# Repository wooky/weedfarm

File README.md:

# weedfarm
An overcomplicated, low-cost replacement for the VegeHome Jardin Pro PCB which got damaged due to water leaking from the water reservoir.

## Features
Features of this package include:
* Activating the pump for 1 minute every 30 minutes
* User-configurable time to turn the lamp on and off
* Driven by an external Android device connected to the custom PCB over USB, which holds the schedule and user configuration
* Ability to charge said device over USB

## Structure
This package is split up into subdirectories:
* pcb: the actual PCB to be manufactured and populated
* firmware: the extra firmware code that would need to be loaded onto the microcontroller on the PCB; it switches the pump and lamp when commanded by the Android device
* android: an Android module which holds the pump and lamp schedule and is used to connect, monitor, and control the PCB over a USB connection

## Old Versions
[esphome](https://github.com/wooky/weedfarm/tree/esphome): a reusable package that can be used on an ESPHome installation which controls everything (but is bulky and only works over WiFi)

## License
This project is licensed under the GNU Affero General Public License v3.0. See [LICENSE](LICENSE) for details.

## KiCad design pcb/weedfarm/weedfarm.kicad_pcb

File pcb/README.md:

# PCB

Replacement controller board for the VegeHome Jardin Pro. It mounts where the original board was. The Android phone holds the schedule, and this board only switches the loads when the phone tells it to.

## Manufacturing

- Designed in EasyEDA, then manufactured and assembled by JLCPCB.
- Prefer JLCPCB basic parts where possible, to avoid extended-part setup fees.
- The barrel jack and USB-A connector are soldered by hand, not by JLCPCB.
- JLCPCB has no MCU in its basic library. The CH32X035G8U6 (C7437027) is an extended part, so it adds the extended-part setup fee.

## Power

| Rail | Source | Feeds |
|------|--------|-------|
| 12V | DC adapter via barrel jack, through a reverse-polarity Schottky (SS54) | Pump; external lamp booster; buck regulator |
| 5V | LM2596S-ADJ buck from 12V, set to about 5.3V | 3.3V LDO; USB-A VBUS through a Schottky (SS34), so VBUS sits near 5V |
| 3.3V | XC6206P332MR LDO from 5V | CH32X035 |

The diode between 5V and VBUS drops the buck's 5.3V to about 5V and stops anything plugged into the USB port from back-feeding the buck. The board needs the 12V adapter to run, including while it's being programmed.

## Microcontroller

- CH32X035G8U6 (WCH, RISC-V, 4x4mm QFN-28), about $0.54 at JLCPCB. It's the cheapest MCU found there with USB host support that needs no crystal.
- No crystal. Per the datasheet, the USBFS module's 48MHz clock comes directly from the internal HSI.
  - USB full-speed allows ±0.25% clock error. Check the HSI accuracy figure in the datasheet. If it's looser, the link depends on the phone's tolerance, so test with the actual phone, including at warm temperatures under the lamp.
- USB full-speed **host** on PC16 (UDM) / PC17 (UDP). The 15kΩ D+/D- pull-downs are internal: WCH's host examples set the pins to input pull-down. No external USB resistors are fitted.
- Pins: PA0 drives the pump, PA1 the lamp, and PA2 the status LED (active low). PC14/CC1 and PC15/CC2 (USB-PD) are unused.
- Programming and debug: a 1x6 header (3.3V, DIO, DCK, TX, RX, GND).
  - Flash over WCH's 2-wire SDI (PC18 DIO / PC19 DCK) with a WCH-LinkE.
  - USART1 (PB10 TX / PB11 RX) for logs, since the USB port is in use by the phone.
  - This package has no NRST or BOOT pin.
- WCH's [EVT examples](https://github.com/openwch/ch32x035) include USBFS host code (`EVT/EXAM/USB/USBFS/HOST_*`) to start the firmware from.

## Loads

- **Pump:** 12V, switched on the low side by a logic-level N-MOSFET (e.g. AO3400A) with a flyback diode across the pump.
- **Lamp:** 12V to an external booster, also switched on the low side by a logic-level N-MOSFET.
- Both loads connect through screw terminals.
- The board has no sensors or buttons. It only drives these two outputs.

## USB / phone link

- The board is the USB host and the phone is an ordinary USB device. A standard USB-A to phone cable plugs into the board's USB-A port.
- The phone charges from VBUS while it's connected, because a phone in device mode charges like it does on any charger. This replaces the earlier ACA approach, which needed a custom cable with an ID resistor and support from the phone.
- Data uses [Android Open Accessory (AOA)](https://source.android.com/docs/core/interaction/accessories/protocol). The board sends the AOA control requests, the phone re-enumerates as an accessory, and the Android app talks to it through the `UsbAccessory` API with bulk transfers. No root is needed.
- The phone has a micro-USB port. The exact model hasn't been chosen.

## Open items

- **Charging current:** without BC1.2 charging-downstream-port signaling, the phone will likely draw only about 500 mA. Shorting D+ to D- (dedicated-charger signaling) would break the data link. Check that 500 mA keeps the chosen phone charged with its normal usage, for example by plugging it into a PC USB 2.0 port with the screen on. If it doesn't, add a CDP controller.
- **HSI accuracy in host mode:** see the Microcontroller section.
- **Board outline:** still to be measured from the original Jardin Pro PCB. This includes the outline dimensions, mounting holes, and connector positions.
- **Load currents:** measure the pump and lamp booster current draw, to size the MOSFETs, traces, and adapter.
- **Part selection:** confirm the JLCPCB part numbers and stock for all components. The LCSC numbers in the sample design are unverified.

## Sample design (KiCad)

[`weedfarm/`](weedfarm/) holds a sample schematic and board, both generated from [`tools/design.py`](tools/design.py). That file is the only place parts, nets, and placement are defined. Edit it, then regenerate:

```sh
python3 pcb/tools/generate.py   # needs KiCad 10 (uses its pcbnew Python module)
cd pcb/weedfarm
kicad-cli sch erc weedfarm.kicad_sch
kicad-cli pcb drc --schematic-parity weedfarm.kicad_pcb
```

Regenerating overwrites both KiCad files, so any edits made in the KiCad GUI are lost.

Current state:

- **Schematic:** ERC has no errors, and its exported netlist matches `design.py`. Connections are made with net labels, not drawn wires.
- **Board:** 104 x 72 mm, two layers, with a GND pour on the bottom. Parts are placed but not routed, so DRC reports unconnected items, plus a few cosmetic silkscreen warnings.
- **Not done:** routing, an outline and mounting holes matching the Jardin Pro, Gerbers, and a JLCPCB BOM/CPL.

To finish the design in EasyEDA Pro, import the KiCad project and route it there (EasyEDA has an autorouter).

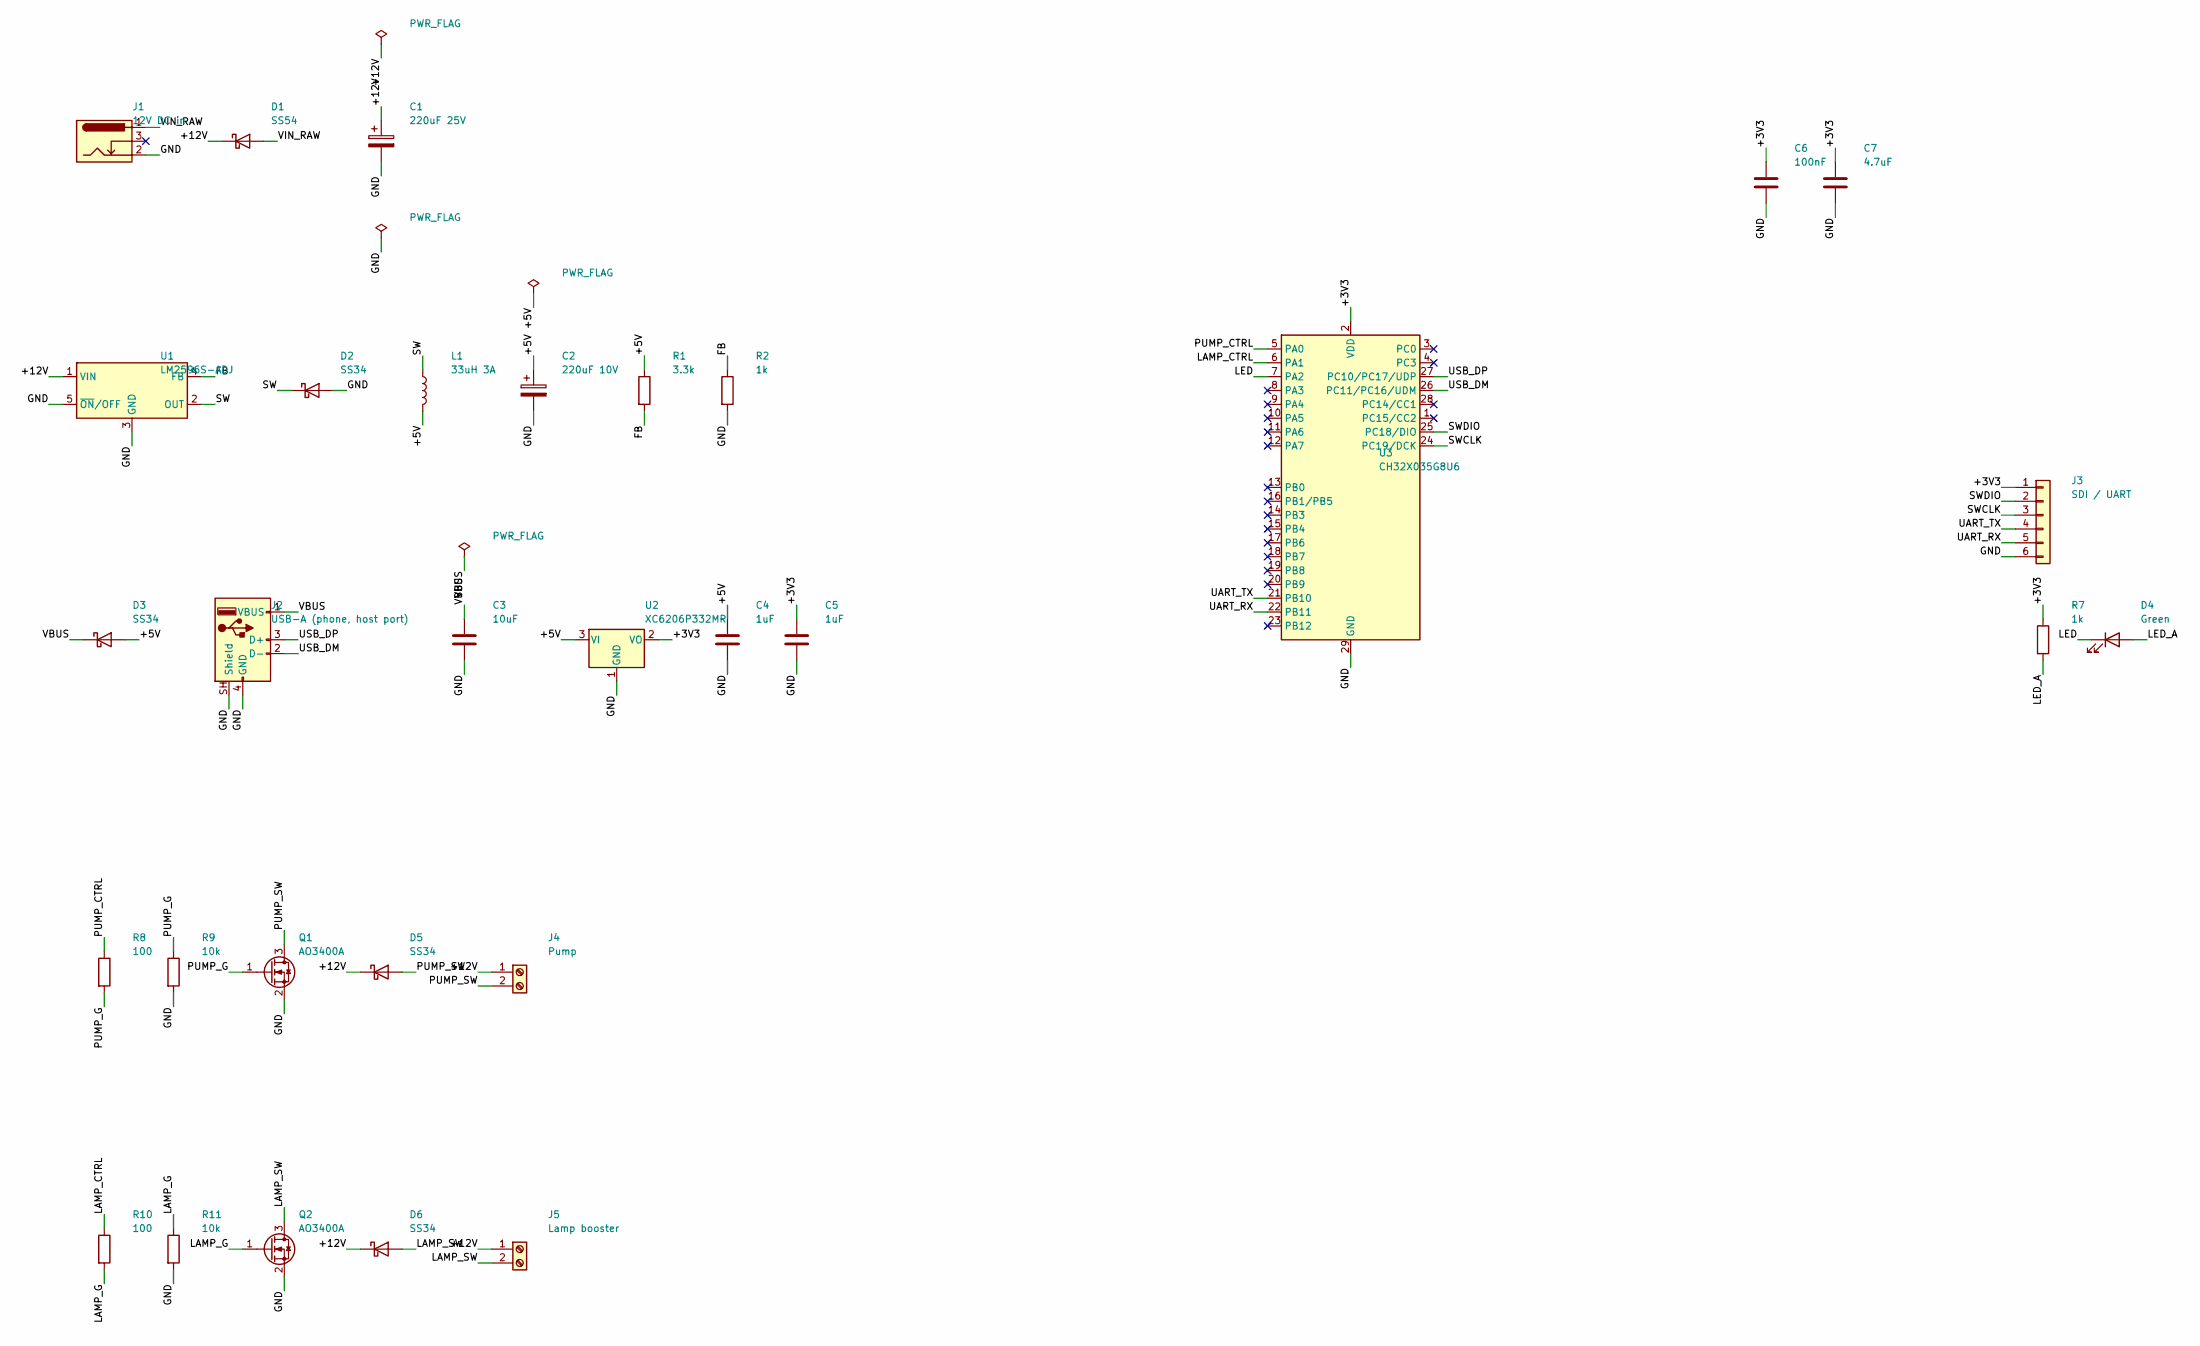
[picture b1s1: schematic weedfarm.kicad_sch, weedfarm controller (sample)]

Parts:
C1: 220uF 25V; CP_Elec_10x10
C2: 220uF 10V; CP_Elec_8x10
C3: 10uF; C_0805_2012Metric
C4, C5: 1uF; C_0603_1608Metric
C6: 100nF; C_0603_1608Metric
C7: 4.7uF; C_0805_2012Metric
D1: SS54; D_SMC
D2, D3, D5, D6: SS34; D_SMA; LCSC C8678
D4: Green; LED_0603_1608Metric
J1: 12V DC in; BarrelJack_Horizontal
J2: USB-A (phone, host port); USB_A_Molex_67643_Horizontal
J3: SDI / UART; PinHeader_1x06_P2.54mm_Vertical
J4: Pump; TerminalBlock_Phoenix_MKDS-1,5-2-5.08_1x02_P5.08mm_Horizont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
J5: Lamp booster; TerminalBlock_Phoenix_MKDS-1,5-2-5.08_1x02_P5.08mm_Horizont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
L1: 33uH 3A; L_12x12mm_H8mm
Q1, Q2: AO3400A; SOT-23; LCSC C20917
R1: 3.3k; R_0603_1608Metric
R2, R7: 1k; R_0603_1608Metric
R8, R10: 100; R_0603_1608Metric
R9, R11: 10k; R_0603_1608Metric
U1: LM2596S-ADJ; TO-263-5_TabPin3
U2: XC6206P332MR; SOT-23-3; LCSC C5446
U3: CH32X035G8U6; WQFN-28-1EP_4x4mm_P0.4mm_EP2.7x2.7mm; LCSC C7437027

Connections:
/+3V3: C5.1, C6.1, C7.1, J3.1, R7.1, U2.2 (VO), U3.2 (VDD)
/+5V: C2.1, C4.1, D3.2 (A), L1.2, R1.1, U2.3 (VI)
/+12V: C1.1, D1.1 (K), D5.1 (K), D6.1 (K), J4.1, J5.1, U1.1 (VIN)
/FB: R1.2, R2.1, U1.4 (FB)
/GND: C1.2, C2.2, C3.2, C4.2, C5.2, C6.2, C7.2, D2.2 (A), J1.2, J2.4 (GND), J2.SH (Shield), J3.6, Q1.2 (S), Q2.2 (S), R2.2, R9.2, R11.2, U1.3 (GND), U1.5 (~ON/OFF), U2.1 (GND), U3.29 (GND)
/LAMP_CTRL: R10.1, U3.6 (PA1)
/LAMP_G: Q2.1 (G), R10.2, R11.1
/LAMP_SW: D6.2 (A), J5.2, Q2.3 (D)
/LED: D4.1 (K), U3.7 (PA2)
/LED_A: D4.2 (A), R7.2
/PUMP_CTRL: R8.1, U3.5 (PA0)
/PUMP_G: Q1.1 (G), R8.2, R9.1
/PUMP_SW: D5.2 (A), J4.2, Q1.3 (D)
/SW: D2.1 (K), L1.1, U1.2 (OUT)
/SWCLK: J3.3, U3.24 (PC19/DCK)
/SWDIO: J3.2, U3.25 (PC18/DIO)
/UART_RX: J3.5, U3.22 (PB11)
/UART_TX: J3.4, U3.21 (PB10)
/USB_DM: J2.2 (D-), U3.26 (PC11/PC16/UDM)
/USB_DP: J2.3 (D+), U3.27 (PC10/PC17/UDP)
/VBUS: C3.1, D3.1 (K), J2.1 (VBUS)
/VIN_RAW: D1.2 (A), J1.1

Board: 2 copper layers, 31 parts (0 on the bottom side), 22 nets, no tracks yet.

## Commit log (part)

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2026-03-08 Add esphome config
2026-03-14 Record boot times and prevent reboot every 15 minutes
2026-05-03 Convert device to a reusable package
